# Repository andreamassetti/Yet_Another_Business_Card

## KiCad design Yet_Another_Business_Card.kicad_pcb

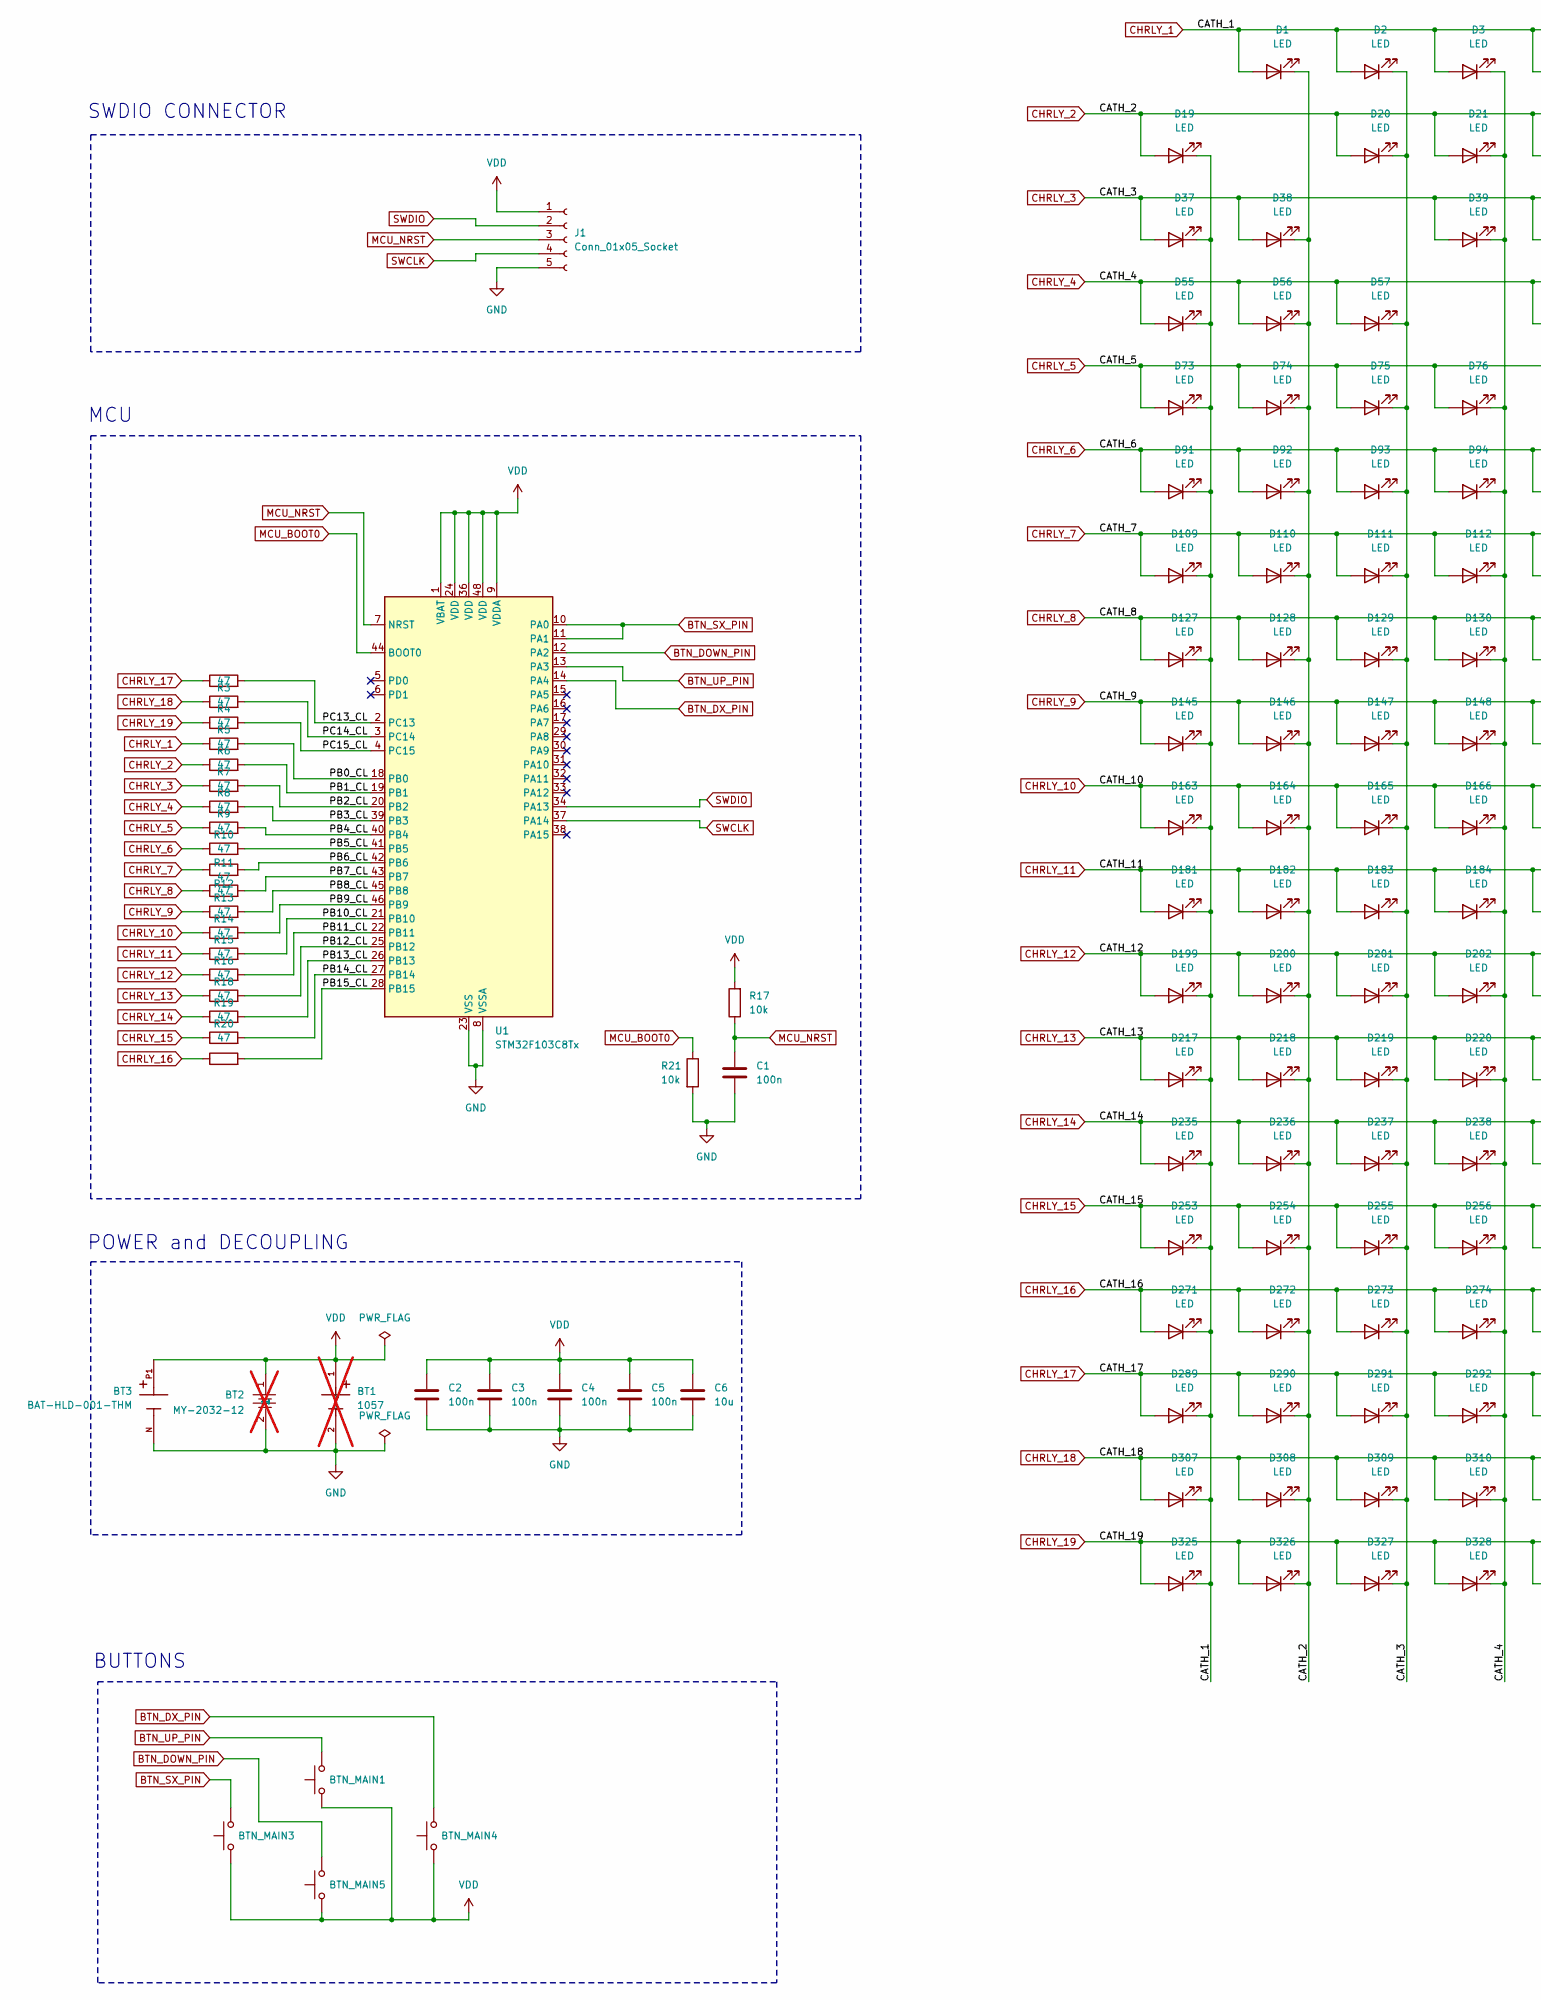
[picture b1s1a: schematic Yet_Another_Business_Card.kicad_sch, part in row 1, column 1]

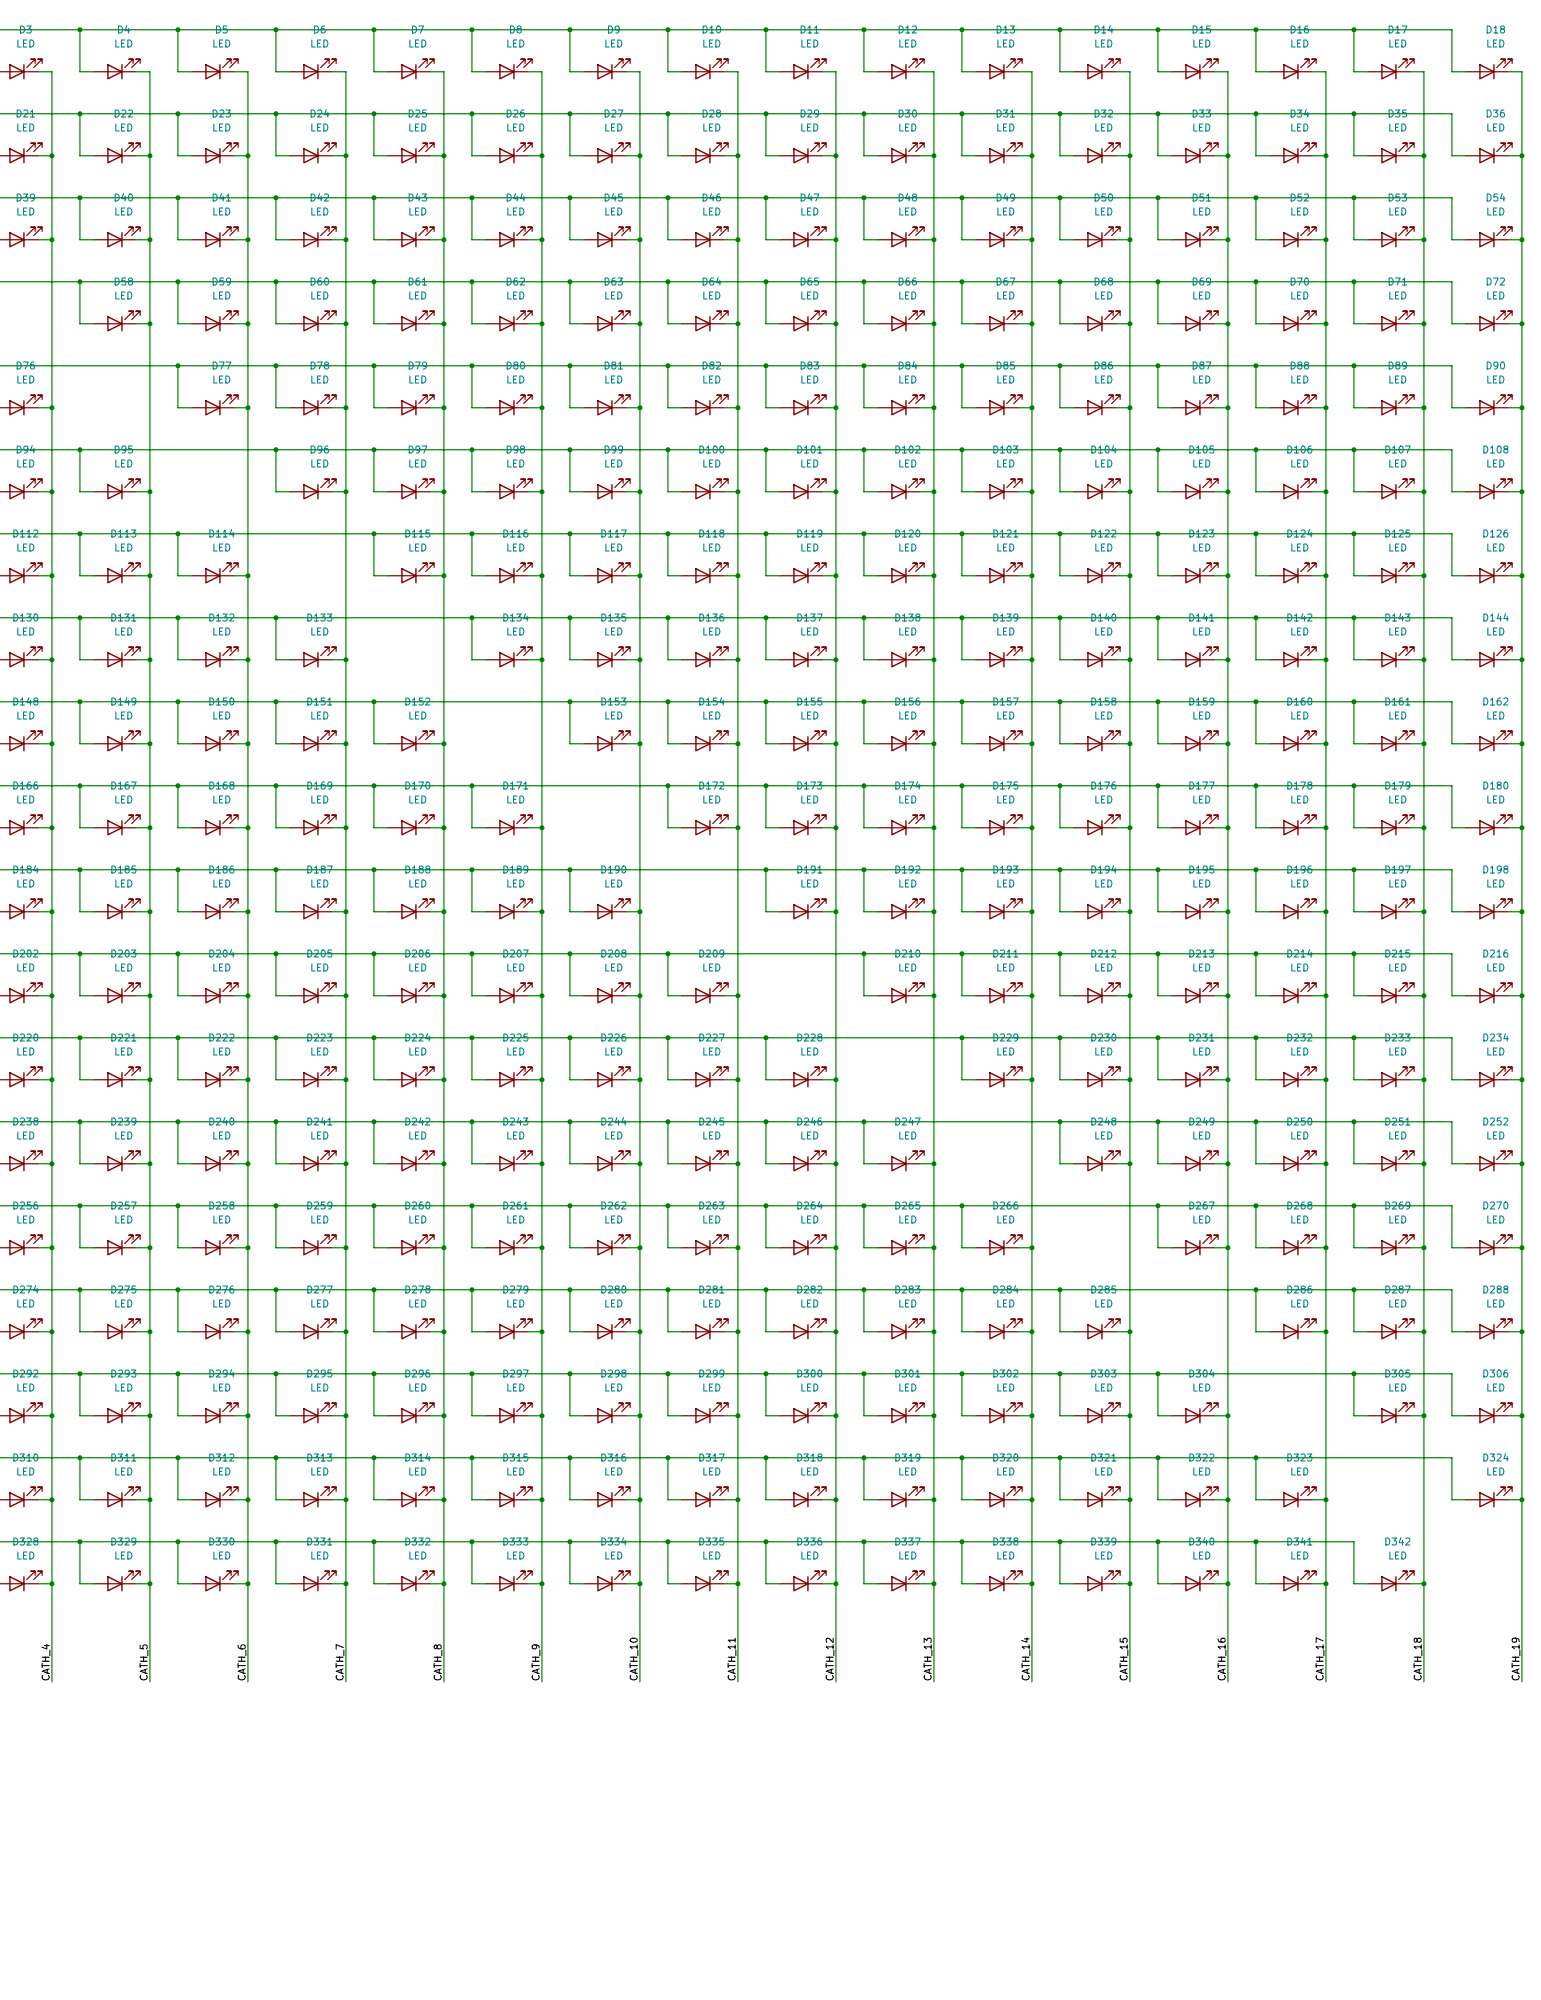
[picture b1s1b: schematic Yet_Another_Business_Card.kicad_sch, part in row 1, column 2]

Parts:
BT1: 1057; BatteryHolder_Keystone_1057_1x2032; PARTREV H; not fitted
BT2: MY-2032-12; BAT-SMD_MY-2032-12; LCSC Part C964833; not fitted
BT3: BAT-HLD-001-THM; BAT_BAT-HLD-001-THM
BTN_MAIN1, BTN_MAIN3, BTN_MAIN4, BTN_MAIN5: SW_Push; SW_Push_1P1T_XKB_TS-1187A
C1, C2, C3, C4, C5: 100n; C_0603_1608Metric
C6: 10u; C_0603_1608Metric
D1, D2, D3, D4, D5, D6, D7, D8, D9, D10, D11, D12, D13, D14, D15, D16, D17, D18, D19, D20, D21, D22, D23, D24, D25, D26, D27, D28, D29, D30, D31, D32, D33, D34, D35, D36, D37, D38, D39, D40, D41, D42, D43, D44, D45, D46, D47, D48, D49, D50, D51, D52, D53, D54, D55, D56, D57, D58, D59, D60, D61, D62, D63, D64, D65, D66, D67, D68, D69, D70, D71, D72, D73, D74, D75, D76, D77, D78, D79, D80, D81, D82, D83, D84, D85, D86, D87, D88, D89, D90, D91, D92, D93, D94, D95, D96, D97, D98, D99, D100, D101, D102, D103, D104, D105, D106, D107, D108, D109, D110, D111, D112, D113, D114, D115, D116, D117, D118, D119, D120, D121, D122, D123, D124, D125, D126, D127, D128, D129, D130, D131, D132, D133, D134, D135, D136, D137, D138, D139, D140, D141, D142, D143, D144, D145, D146, D147, D148, D149, D150, D151, D152, D153, D154, D155, D156, D157, D158, D159, D160, D161, D162, D163, D164, D165, D166, D167, D168, D169, D170, D171, D172, D173, D174, D175, D176, D177, D178, D179, D180, D181, D182, D183, D184, D185, D186, D187, D188, D189, D190, D191, D192, D193, D194, D195, D196, D197, D198, D199, D200, D201, D202, D203, D204, D205, D206, D207, D208, D209, D210, D211, D212, D213, D214, D215, D216, D217, D218, D219, D220, D221, D222, D223, D224, D225, D226, D227, D228, D229, D230, D231, D232, D233, D234, D235, D236, D237, D238, D239, D240, D241, D242, D243, D244, D245, D246, D247, D248, D249, D250, D251, D252, D253, D254, D255, D256, D257, D258, D259, D260, D261, D262, D263, D264, D265, D266, D267, D268, D269, D270, D271, D272, D273, D274, D275, D276, D277, D278, D279, D280, D281, D282, D283, D284, D285, D286, D287, D288, D289, D290, D291, D292, D293, D294, D295, D296, D297, D298, D299, D300, D301, D302, D303, D304, D305, D306, D307, D308, D309, D310, D311, D312, D313, D314, D315, D316, D317, D318, D319, D320, D321, D322, D323, D324, D325, D326, D327, D328, D329, D330, D331, D332, D333, D334, D335, D336, D337, D338, D339, D340, D341, D342: LED; LED_0603_no_silkscreen
J1: Conn_01x05_Socket; PinSocket_1x05_P2.54mm_Vertical
R1, R2, R3, R4, R5, R6, R7, R8, R9, R10, R11, R12, R13, R14, R15, R16, R18, R19, R20: 47; R_0603_1608Metric
R17, R21: 10k; R_0603_1608Metric
U1: STM32F103C8Tx; LQFP-48_7x7mm_P0.5mm

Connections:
/PB0_CL: R4.2, U1.18 (PB0)
/PB1_CL: R5.2, U1.19 (PB1)
/PB2_CL: R6.2, U1.20 (PB2)
/PB3_CL: R7.2, U1.39 (PB3)
/PB4_CL: R8.2, U1.40 (PB4)
/PB5_CL: R9.2, U1.41 (PB5)
/PB6_CL: R10.2, U1.42 (PB6)
/PB7_CL: R11.2, U1.43 (PB7)
/PB8_CL: R12.2, U1.45 (PB8)
/PB9_CL: R13.2, U1.46 (PB9)
/PB10_CL: R14.2, U1.21 (PB10)
/PB11_CL: R15.2, U1.22 (PB11)
/PB12_CL: R16.2, U1.25 (PB12)
/PB13_CL: R18.2, U1.26 (PB13)
/PB14_CL: R19.2, U1.27 (PB14)
/PB15_CL: R20.2, U1.28 (PB15)
/PC13_CL: R1.2, U1.2 (PC13)
/PC14_CL: R2.2, U1.3 (PC14)
/PC15_CL: R3.2, U1.4 (PC15)
BTN_DOWN_PIN: BTN_MAIN5.2, U1.12 (PA2)
BTN_DX_PIN: BTN_MAIN4.2, U1.14 (PA4)
BTN_SX_PIN: BTN_MAIN3.2, U1.10 (PA0), U1.11 (PA1)
BTN_UP_PIN: BTN_MAIN1.2, U1.13 (PA3)
CHRLY_1: D1.2 (A), D2.2 (A), D3.2 (A), D4.2 (A), D5.2 (A), D6.2 (A), D7.2 (A), D8.2 (A), D9.2 (A), D10.2 (A), D11.2 (A), D12.2 (A), D13.2 (A), D14.2 (A), D15.2 (A), D16.2 (A), D17.2 (A), D18.2 (A), D19.1 (K), D37.1 (K), D55.1 (K), D73.1 (K), D91.1 (K), D109.1 (K), D127.1 (K), D145.1 (K), D163.1 (K), D181.1 (K), D199.1 (K), D217.1 (K), D235.1 (K), D253.1 (K), D271.1 (K), D289.1 (K), D307.1 (K), D325.1 (K), R4.1
CHRLY_2: D1.1 (K), D19.2 (A), D20.2 (A), D21.2 (A), D22.2 (A), D23.2 (A), D24.2 (A), D25.2 (A), D26.2 (A), D27.2 (A), D28.2 (A), D29.2 (A), D30.2 (A), D31.2 (A), D32.2 (A), D33.2 (A), D34.2 (A), D35.2 (A), D36.2 (A), D38.1 (K), D56.1 (K), D74.1 (K), D92.1 (K), D110.1 (K), D128.1 (K), D146.1 (K), D164.1 (K), D182.1 (K), D200.1 (K), D218.1 (K), D236.1 (K), D254.1 (K), D272.1 (K), D290.1 (K), D308.1 (K), D326.1 (K), R5.1
CHRLY_3: D2.1 (K), D20.1 (K), D37.2 (A), D38.2 (A), D39.2 (A), D40.2 (A), D41.2 (A), D42.2 (A), D43.2 (A), D44.2 (A), D45.2 (A), D46.2 (A), D47.2 (A), D48.2 (A), D49.2 (A), D50.2 (A), D51.2 (A), D52.2 (A), D53.2 (A), D54.2 (A), D57.1 (K), D75.1 (K), D93.1 (K), D111.1 (K), D129.1 (K), D147.1 (K), D165.1 (K), D183.1 (K), D201.1 (K), D219.1 (K), D237.1 (K), D255.1 (K), D273.1 (K), D291.1 (K), D309.1 (K), D327.1 (K), R6.1
CHRLY_4: D3.1 (K), D21.1 (K), D39.1 (K), D55.2 (A), D56.2 (A), D57.2 (A), D58.2 (A), D59.2 (A), D60.2 (A), D61.2 (A), D62.2 (A), D63.2 (A), D64.2 (A), D65.2 (A), D66.2 (A), D67.2 (A), D68.2 (A), D69.2 (A), D70.2 (A), D71.2 (A), D72.2 (A), D76.1 (K), D94.1 (K), D112.1 (K), D130.1 (K), D148.1 (K), D166.1 (K), D184.1 (K), D202.1 (K), D220.1 (K), D238.1 (K), D256.1 (K), D274.1 (K), D292.1 (K), D310.1 (K), D328.1 (K), R7.1
CHRLY_5: D4.1 (K), D22.1 (K), D40.1 (K), D58.1 (K), D73.2 (A), D74.2 (A), D75.2 (A), D76.2 (A), D77.2 (A), D78.2 (A), D79.2 (A), D80.2 (A), D81.2 (A), D82.2 (A), D83.2 (A), D84.2 (A), D85.2 (A), D86.2 (A), D87.2 (A), D88.2 (A), D89.2 (A), D90.2 (A), D95.1 (K), D113.1 (K), D131.1 (K), D149.1 (K), D167.1 (K), D185.1 (K), D203.1 (K), D221.1 (K), D239.1 (K), D257.1 (K), D275.1 (K), D293.1 (K), D311.1 (K), D329.1 (K), R8.1
CHRLY_6: D5.1 (K), D23.1 (K), D41.1 (K), D59.1 (K), D77.1 (K), D91.2 (A), D92.2 (A), D93.2 (A), D94.2 (A), D95.2 (A), D96.2 (A), D97.2 (A), D98.2 (A), D99.2 (A), D100.2 (A), D101.2 (A), D102.2 (A), D103.2 (A), D104.2 (A), D105.2 (A), D106.2 (A), D107.2 (A), D108.2 (A), D114.1 (K), D132.1 (K), D150.1 (K), D168.1 (K), D186.1 (K), D204.1 (K), D222.1 (K), D240.1 (K), D258.1 (K), D276.1 (K), D294.1 (K), D312.1 (K), D330.1 (K), R9.1
CHRLY_7: D6.1 (K), D24.1 (K), D42.1 (K), D60.1 (K), D78.1 (K), D96.1 (K), D109.2 (A), D110.2 (A), D111.2 (A), D112.2 (A), D113.2 (A), D114.2 (A), D115.2 (A), D116.2 (A), D117.2 (A), D118.2 (A), D119.2 (A), D120.2 (A), D121.2 (A), D122.2 (A), D123.2 (A), D124.2 (A), D125.2 (A), D126.2 (A), D133.1 (K), D151.1 (K), D169.1 (K), D187.1 (K), D205.1 (K), D223.1 (K), D241.1 (K), D259.1 (K), D277.1 (K), D295.1 (K), D313.1 (K), D331.1 (K), R10.1
CHRLY_8: D7.1 (K), D25.1 (K), D43.1 (K), D61.1 (K), D79.1 (K), D97.1 (K), D115.1 (K), D127.2 (A), D128.2 (A), D129.2 (A), D130.2 (A), D131.2 (A), D132.2 (A), D133.2 (A), D134.2 (A), D135.2 (A), D136.2 (A), D137.2 (A), D138.2 (A), D139.2 (A), D140.2 (A), D141.2 (A), D142.2 (A), D143.2 (A), D144.2 (A), D152.1 (K), D170.1 (K), D188.1 (K), D206.1 (K), D224.1 (K), D242.1 (K), D260.1 (K), D278.1 (K), D296.1 (K), D314.1 (K), D332.1 (K), R11.1
CHRLY_9: D8.1 (K), D26.1 (K), D44.1 (K), D62.1 (K), D80.1 (K), D98.1 (K), D116.1 (K), D134.1 (K), D145.2 (A), D146.2 (A), D147.2 (A), D148.2 (A), D149.2 (A), D150.2 (A), D151.2 (A), D152.2 (A), D153.2 (A), D154.2 (A), D155.2 (A), D156.2 (A), D157.2 (A), D158.2 (A), D159.2 (A), D160.2 (A), D161.2 (A), D162.2 (A), D171.1 (K), D189.1 (K), D207.1 (K), D225.1 (K), D243.1 (K), D261.1 (K), D279.1 (K), D297.1 (K), D315.1 (K), D333.1 (K), R12.1
CHRLY_10: D9.1 (K), D27.1 (K), D45.1 (K), D63.1 (K), D81.1 (K), D99.1 (K), D117.1 (K), D135.1 (K), D153.1 (K), D163.2 (A), D164.2 (A), D165.2 (A), D166.2 (A), D167.2 (A), D168.2 (A), D169.2 (A), D170.2 (A), D171.2 (A), D172.2 (A), D173.2 (A), D174.2 (A), D175.2 (A), D176.2 (A), D177.2 (A), D178.2 (A), D179.2 (A), D180.2 (A), D190.1 (K), D208.1 (K), D226.1 (K), D244.1 (K), D262.1 (K), D280.1 (K), D298.1 (K), D316.1 (K), D334.1 (K), R13.1
CHRLY_11: D10.1 (K), D28.1 (K), D46.1 (K), D64.1 (K), D82.1 (K), D100.1 (K), D118.1 (K), D136.1 (K), D154.1 (K), D172.1 (K), D181.2 (A), D182.2 (A), D183.2 (A), D184.2 (A), D185.2 (A), D186.2 (A), D187.2 (A), D188.2 (A), D189.2 (A), D190.2 (A), D191.2 (A), D192.2 (A), D193.2 (A), D194.2 (A), D195.2 (A), D196.2 (A), D197.2 (A), D198.2 (A), D209.1 (K), D227.1 (K), D245.1 (K), D263.1 (K), D281.1 (K), D299.1 (K), D317.1 (K), D335.1 (K), R14.1
CHRLY_12: D11.1 (K), D29.1 (K), D47.1 (K), D65.1 (K), D83.1 (K), D101.1 (K), D119.1 (K), D137.1 (K), D155.1 (K), D173.1 (K), D191.1 (K), D199.2 (A), D200.2 (A), D201.2 (A), D202.2 (A), D203.2 (A), D204.2 (A), D205.2 (A), D206.2 (A), D207.2 (A), D208.2 (A), D209.2 (A), D210.2 (A), D211.2 (A), D212.2 (A), D213.2 (A), D214.2 (A), D215.2 (A), D216.2 (A), D228.1 (K), D246.1 (K), D264.1 (K), D282.1 (K), D300.1 (K), D318.1 (K), D336.1 (K), R15.1
CHRLY_13: D12.1 (K), D30.1 (K), D48.1 (K), D66.1 (K), D84.1 (K), D102.1 (K), D120.1 (K), D138.1 (K), D156.1 (K), D174.1 (K), D192.1 (K), D210.1 (K), D217.2 (A), D218.2 (A), D219.2 (A), D220.2 (A), D221.2 (A), D222.2 (A), D223.2 (A), D224.2 (A), D225.2 (A), D226.2 (A), D227.2 (A), D228.2 (A), D229.2 (A), D230.2 (A), D231.2 (A), D232.2 (A), D233.2 (A), D234.2 (A), D247.1 (K), D265.1 (K), D283.1 (K), D301.1 (K), D319.1 (K), D337.1 (K), R16.1
CHRLY_14: D13.1 (K), D31.1 (K), D49.1 (K), D67.1 (K), D85.1 (K), D103.1 (K), D121.1 (K), D139.1 (K), D157.1 (K), D175.1 (K), D193.1 (K), D211.1 (K), D229.1 (K), D235.2 (A), D236.2 (A), D237.2 (A), D238.2 (A), D239.2 (A), D240.2 (A), D241.2 (A), D242.2 (A), D243.2 (A), D244.2 (A), D245.2 (A), D246.2 (A), D247.2 (A), D248.2 (A), D249.2 (A), D250.2 (A), D251.2 (A), D252.2 (A), D266.1 (K), D284.1 (K), D302.1 (K), D320.1 (K), D338.1 (K), R18.1
CHRLY_15: D14.1 (K), D32.1 (K), D50.1 (K), D68.1 (K), D86.1 (K), D104.1 (K), D122.1 (K), D140.1 (K), D158.1 (K), D176.1 (K), D194.1 (K), D212.1 (K), D230.1 (K), D248.1 (K), D253.2 (A), D254.2 (A), D255.2 (A), D256.2 (A), D257.2 (A), D258.2 (A), D259.2 (A), D260.2 (A), D261.2 (A), D262.2 (A), D263.2 (A), D264.2 (A), D265.2 (A), D266.2 (A), D267.2 (A), D268.2 (A), D269.2 (A), D270.2 (A), D285.1 (K), D303.1 (K), D321.1 (K), D339.1 (K), R19.1
CHRLY_16: D15.1 (K), D33.1 (K), D51.1 (K), D69.1 (K), D87.1 (K), D105.1 (K), D123.1 (K), D141.1 (K), D159.1 (K), D177.1 (K), D195.1 (K), D213.1 (K), D231.1 (K), D249.1 (K), D267.1 (K), D271.2 (A), D272.2 (A), D273.2 (A), D274.2 (A), D275.2 (A), D276.2 (A), D277.2 (A), D278.2 (A), D279.2 (A), D280.2 (A), D281.2 (A), D282.2 (A), D283.2 (A), D284.2 (A), D285.2 (A), D286.2 (A), D287.2 (A), D288.2 (A), D304.1 (K), D322.1 (K), D340.1 (K), R20.1
CHRLY_17: D16.1 (K), D34.1 (K), D52.1 (K), D70.1 (K), D88.1 (K), D106.1 (K), D124.1 (K), D142.1 (K), D160.1 (K), D178.1 (K), D196.1 (K), D214.1 (K), D232.1 (K), D250.1 (K), D268.1 (K), D286.1 (K), D289.2 (A), D290.2 (A), D291.2 (A), D292.2 (A), D293.2 (A), D294.2 (A), D295.2 (A), D296.2 (A), D297.2 (A), D298.2 (A), D299.2 (A), D300.2 (A), D301.2 (A), D302.2 (A), D303.2 (A), D304.2 (A), D305.2 (A), D306.2 (A), D323.1 (K), D341.1 (K), R1.1
CHRLY_18: D17.1 (K), D35.1 (K), D53.1 (K), D71.1 (K), D89.1 (K), D107.1 (K), D125.1 (K), D143.1 (K), D161.1 (K), D179.1 (K), D197.1 (K), D215.1 (K), D233.1 (K), D251.1 (K), D269.1 (K), D287.1 (K), D305.1 (K), D307.2 (A), D308.2 (A), D309.2 (A), D310.2 (A), D311.2 (A), D312.2 (A), D313.2 (A), D314.2 (A), D315.2 (A), D316.2 (A), D317.2 (A), D318.2 (A), D319.2 (A), D320.2 (A), D321.2 (A), D322.2 (A), D323.2 (A), D324.2 (A), D342.1 (K), R2.1
CHRLY_19: D18.1 (K), D36.1 (K), D54.1 (K), D72.1 (K), D90.1 (K), D108.1 (K), D126.1 (K), D144.1 (K), D162.1 (K), D180.1 (K), D198.1 (K), D216.1 (K), D234.1 (K), D252.1 (K), D270.1 (K), D288.1 (K), D306.1 (K), D324.1 (K), D325.2 (A), D326.2 (A), D327.2 (A), D328.2 (A), D329.2 (A), D330.2 (A), D331.2 (A), D332.2 (A), D333.2 (A), D334.2 (A), D335.2 (A), D336.2 (A), D337.2 (A), D338.2 (A), D339.2 (A), D340.2 (A), D341.2 (A), D342.2 (A), R3.1
GND: BT1.2 (-), BT2.2, BT3.N, C1.2, C2.2, C3.2, C4.2, C5.2, C6.2, J1.5, R21.2, U1.8 (VSSA), U1.23 (VSS), U1.35 (VSS), U1.47 (VSS)
MCU_BOOT0: R21.1, U1.44 (BOOT0)
MCU_NRST: C1.1, J1.3, R17.1, U1.7 (NRST)
SWCLK: J1.4, U1.37 (PA14)
SWDIO: J1.2, U1.34 (PA13)
VDD: BT1.1 (+), BT2.1, BT3.P1, BT3.P2, BT3.P3, BT3.P4, BTN_MAIN1.1, BTN_MAIN3.1, BTN_MAIN4.1, BTN_MAIN5.1, C2.1, C3.1, C4.1, C5.1, C6.1, J1.1, R17.2, U1.1 (VBAT), U1.9 (VDDA), U1.24 (VDD), U1.36 (VDD), U1.48 (VDD)

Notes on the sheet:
SWDIO CONNECTOR
MCU
BUTTONS
POWER and DECOUPLING

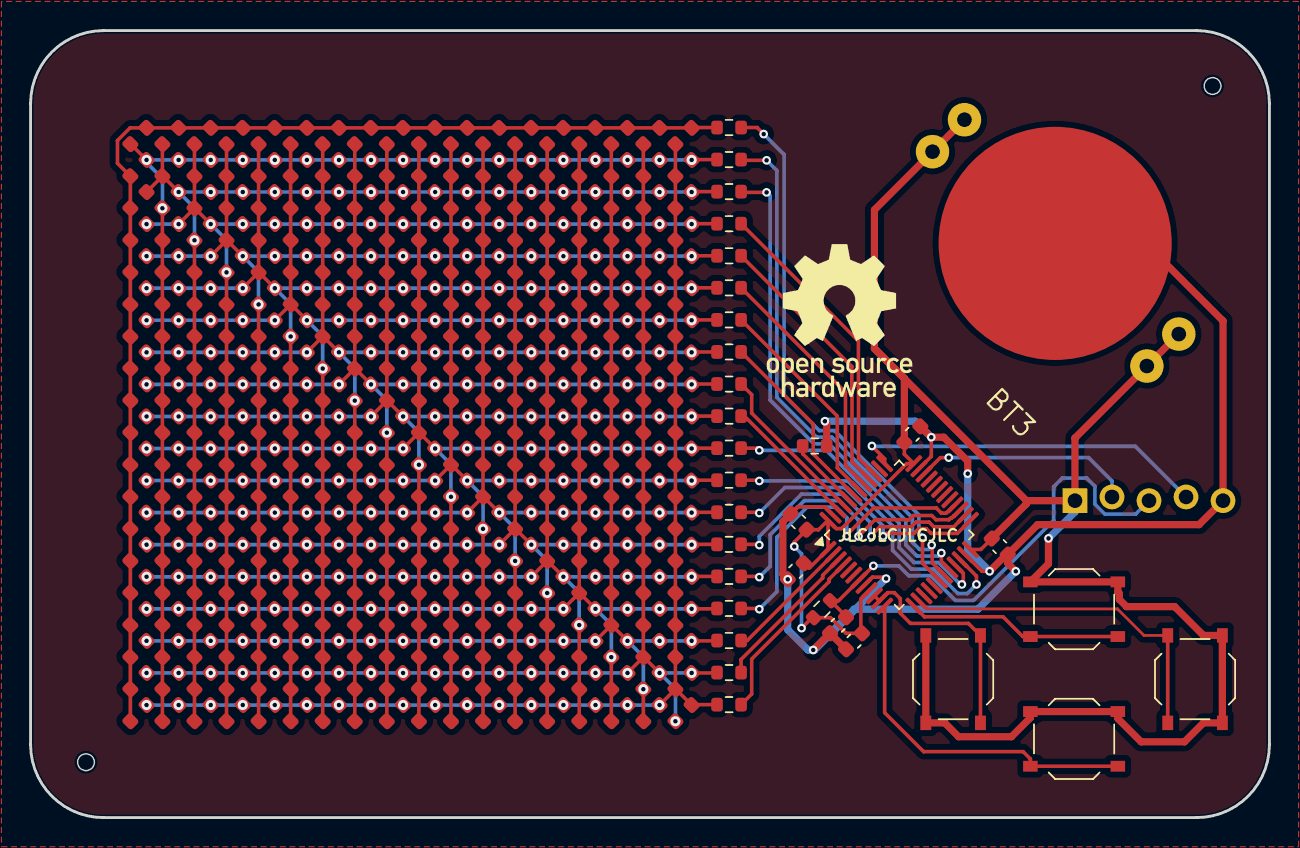
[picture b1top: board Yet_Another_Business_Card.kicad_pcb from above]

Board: 2 copper layers, 85.0 x 54.0 mm, 376 parts (0 on the bottom side), 48 nets.

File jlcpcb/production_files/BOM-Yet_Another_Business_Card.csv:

Comment,Designator,Footprint,LCSC,Quantity
100n,"C1,C2,C3,C4,C5",C_0603_1608Metric,C14663,5
10u,C6,C_0603_1608Metric,C19702,1
LED,"D1,D10,D100,D101,D102,D103,D104,D105,D106,D107,D108,D109,D11,D110,D111,D112,D113,D114,D115,D116,D117,D118,D119,D12,D120,D121,D122,D123,D124,D125,D126,D127,D128,D129,D13,D130,D131,D132,D133,D134,D135,D136,D137,D138,D139,D14,D140,D141,D142,D143,D144,D145,D146,D147,D148,D149,D15,D150,D151,D152,D153,D154,D155,D156,D157,D158,D159,D16,D160,D161,D162,D163,D164,D165,D166,D167,D168,D169,D17,D170,D171,D172,D173,D174,D175,D176,D177,D178,D179,D18,D180,D181,D182,D183,D184,D185,D186,D187,D188,D189,D19,D190,D191,D192,D193,D194,D195,D196,D197,D198,D199,D2,D20,D200,D201,D202,D203,D204,D205,D206,D207,D208,D209,D21,D210,D211,D212,D213,D214,D215,D216,D217,D218,D219,D22,D220,D221,D222,D223,D224,D225,D226,D227,D228,D229,D23,D230,D231,D232,D233,D234,D235,D236,D237,D238,D239,D24,D240,D241,D242,D243,D244,D245,D246,D247,D248,D249,D25,D250,D251,D252,D253,D254,D255,D256,D257,D258,D259,D26,D260,D261,D262,D263,D264,D265,D266,D267,D268,D269,D27,D270,D271,D272,D273,D274,D275,D276,D277,D278,D279,D28,D280,D281,D282,D283,D284,D285,D286,D287,D288,D289,D29,D290,D291,D292,D293,D294,D295,D296,D297,D298,D299,D3,D30,D300,D301,D302,D303,D304,D305,D306,D307,D308,D309,D31,D310,D311,D312,D313,D314,D315,D316,D317,D318,D319,D32,D320,D321,D322,D323,D324,D325,D326,D327,D328,D329,D33,D330,D331,D332,D333,D334,D335,D336,D337,D338,D339,D34,D340,D341,D342,D35,D36,D37,D38,D39,D4,D40,D41,D42,D43,D44,D45,D46,D47,D48,D49,D5,D50,D51,D52,D53,D54,D55,D56,D57,D58,D59,D6,D60,D61,D62,D63,D64,D65,D66,D67,D68,D69,D7,D70,D71,D72,D73,D74,D75,D76,D77,D78,D79,D8,D80,D81,D82,D83,D84,D85,D86,D87,D88,D89,D9,D90,D91,D92,D93,D94,D95,D96,D97,D98,D99",LED_0603_no_silkscreen,C2290,342
47,"R1,R10,R11,R12,R13,R14,R15,R16,R18,R19,R2,R20,R3,R4,R5,R6,R7,R8,R9",R_0603_1608Metric,C23182,19
10k,"R17,R21",R_0603_1608Metric,C25804,2
SW_Push,"BTN_MAIN1,BTN_MAIN3,BTN_MAIN4,BTN_MAIN5",SW_Push_1P1T_XKB_TS-1187A,C318884,4
STM32F103C8Tx,U1,LQFP-48_7x7mm_P0.5mm,C8734,1

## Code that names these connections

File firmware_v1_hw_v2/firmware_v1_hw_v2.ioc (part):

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Mcu.Name=STM32F103C(8-B)Tx
Mcu.Package=LQFP48
Mcu.UserName=STM32F103C8Tx
PA0-WKUP.Mode=SYS_WakeUp0
PA0-WKUP.Signal=SYS_WKUP
PA1.GPIOParameters=GPIO_PuPd,GPIO_ModeDefaultEXTI
PA1.GPIO_ModeDefaultEXTI=GPIO_MODE_IT_RISING_FALLING
PA1.GPIO_PuPd=GPIO_PULLDOWN
PA1.Signal=GPXTI1
PA13.Mode=Serial_Wire
PA13.Signal=SYS_JTMS-SWDIO
PA14.Mode=Serial_Wire
PA14.Signal=SYS_JTCK-SWCLK
PA2.GPIOParameters=GPIO_PuPd,GPIO_ModeDefaultEXTI
PA2.GPIO_ModeDefaultEXTI=GPIO_MODE_IT_RISING_FALLING
PA2.GPIO_PuPd=GPIO_PULLDOWN
PA2.Signal=GPXTI2
PA3.GPIOParameters=GPIO_PuPd,GPIO_ModeDefaultEXTI
PA3.GPIO_ModeDefaultEXTI=GPIO_MODE_IT_RISING_FALLING
PA3.GPIO_PuPd=GPIO_PULLDOWN
PA3.Signal=GPXTI3
PA4.GPIOParameters=GPIO_PuPd,GPIO_ModeDefaultEXTI
PA4.GPIO_ModeDefaultEXTI=GPIO_MODE_IT_RISING_FALLING
PA4.GPIO_PuPd=GPIO_PULLDOWN
PA4.Signal=GPXTI4
PB0.Signal=GPIO_Output
PB1.GPIOParameters=PinState
PB1.PinState=GPIO_PIN_RESET
PB1.Signal=GPIO_Output
PB10.Signal=GPIO_Output
PB11.Signal=GPIO_Output
PB12.Signal=GPIO_Output
PB13.Signal=GPIO_Output
PB14.Signal=GPIO_Output
PB15.Signal=GPIO_Output
PB2.Signal=GPIO_Output
PB3.Signal=GPIO_Output
PB4.Signal=GPIO_Output
PB5.Signal=GPIO_Output
PB6.Signal=GPIO_Output
PB7.Signal=GPIO_Output
PB8.Signal=GPIO_Output
PB9.Signal=GPIO_Output
PC13-TAMPER-RTC.GPIOParameters=PinState
PC13-TAMPER-RTC.PinState=GPIO_PIN_RESET
PC13-TAMPER-RTC.Signal=GPIO_Output
PC14-OSC32_IN.GPIOParameters=PinState
PC14-OSC32_IN.PinState=GPIO_PIN_SET
PC14-OSC32_IN.Signal=GPIO_Output
PC15-OSC32_OUT.Signal=GPIO_Output
board=custom

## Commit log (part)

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2025-10-11 First revision
2025-10-30 Added first version of firmware to test LEDs, works but some are not turned on
2025-10-30 Added SWDIO connector, python script to convert gif to matrix data
2025-11-11 Updated firmware (v2), first working version with row-driven display!!!!!!
2025-11-13 Finished first version of generic row driver for display, no greyscale support yet
2025-11-21 Working version with only black/white led driver, added python script with GUI to convert gif/video to bidimensional array data
2025-12-18 Updated firmware, PCB files are updated after the second prototype production (added just 2 battery holder footprints as a test)
2026-03-06 firmware_v4 added
2026-03-09 Updated code for compatibility problems on work linux PC, created working implementation of firmware_v2 (YABC_fw_v2) for second version of hardware platform. Working also with WKUP function on PA0.
2026-03-10 Flashed code to second board of hw v2, ordered hw v3 boards
2026-03-30 As gifted to family
2026-06-02 Added greyscale support.
